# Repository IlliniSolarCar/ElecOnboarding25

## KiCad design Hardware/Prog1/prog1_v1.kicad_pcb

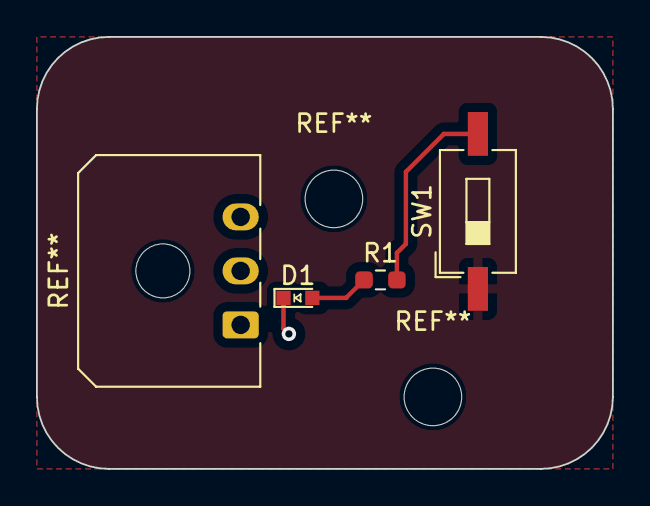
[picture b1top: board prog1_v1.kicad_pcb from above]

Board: 2 copper layers, 32.0 x 24.0 mm, 3 parts (0 on the bottom side), 2 nets.

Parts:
D1: LED_RED; LED_0603_Symbol_on_F.SilkS
R1: 105; R_0603_1608Metric_Pad0.98x0.95mm_HandSolder
SW1: SW_Push; SW_DIP_SPSTx01_Slide_6.7x4.1mm_W8.61mm_P2.54mm_LowProfile

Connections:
unnamed: D1.2 (A), R1.2
unnamed: R1.1, SW1.2

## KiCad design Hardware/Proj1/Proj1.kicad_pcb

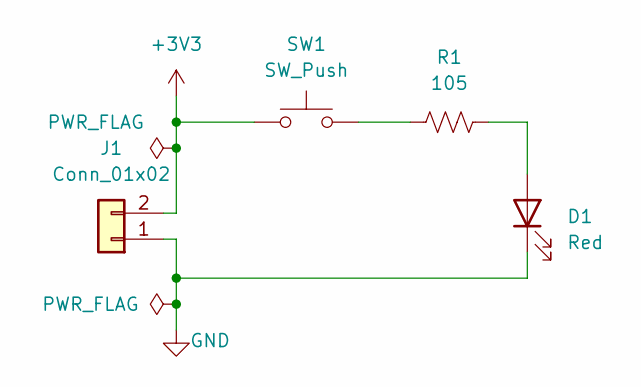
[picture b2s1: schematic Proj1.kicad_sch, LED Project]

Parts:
D1: Red; LED_0603_Symbol_on_F.SilkS
J1: Conn_01x02; Molex_KK-254_AE-6410-02A_1x02_P2.54mm_Vertical; MPN 22-27-2021
R1: 105; R_0603_1608Metric_Pad0.98x0.95mm_HandSolder
SW1: SW_Push; SW_PUSH_6mm; MPN B3F-1000

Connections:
+3V3: J1.2, SW1.1
GND: D1.1 (K), J1.1
unnamed: D1.2 (A), R1.2
unnamed: R1.1, SW1.2

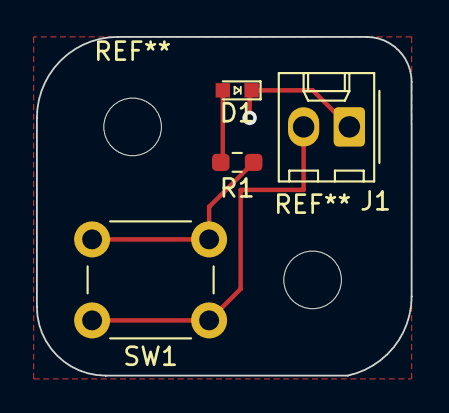
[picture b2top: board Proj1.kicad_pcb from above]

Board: 2 copper layers, 20.8 x 18.8 mm, 4 parts (0 on the bottom side), 4 nets.

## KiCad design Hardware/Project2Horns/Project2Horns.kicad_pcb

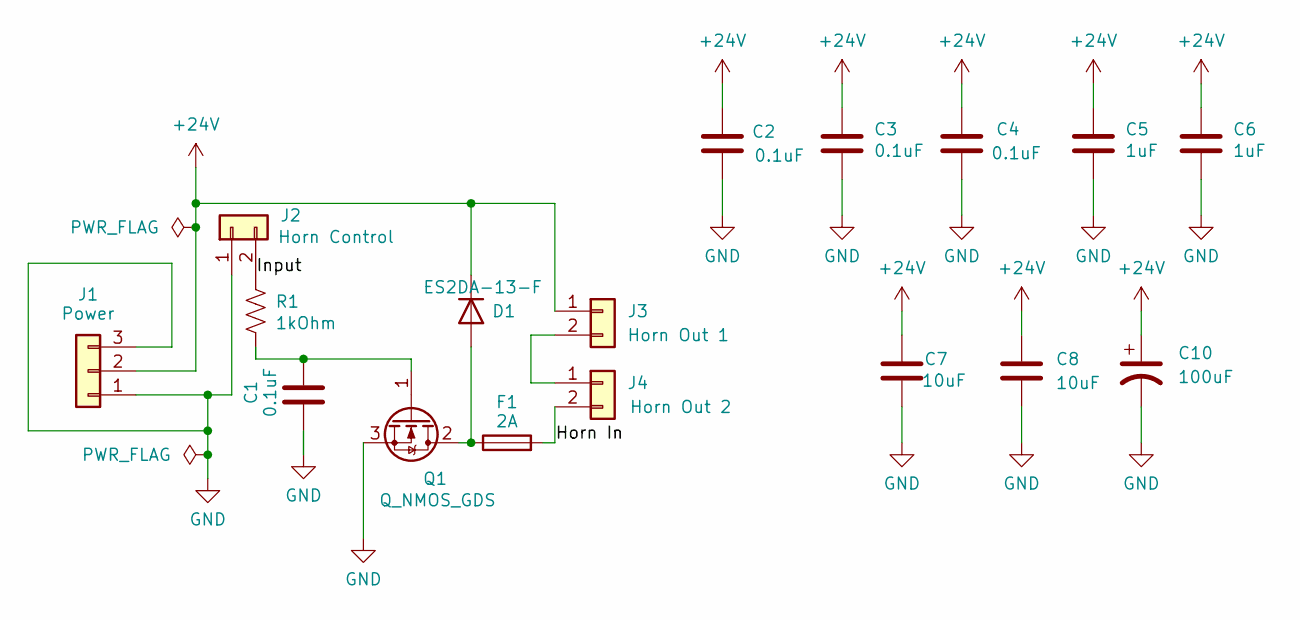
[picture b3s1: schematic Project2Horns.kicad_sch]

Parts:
C1, C2, C3, C4: 0.1uF; C_0603_1608Metric_Pad1.08x0.95mm_HandSolder
C5, C6: 1uF; C_0603_1608Metric_Pad1.08x0.95mm_HandSolder
C7, C8: 10uF; C_0603_1608Metric_Pad1.08x0.95mm_HandSolder
C10: 100uF; CP_Radial_D6.3mm_P2.50mm
D1: ES2DA-13-F; D_SMA_Handsoldering
F1: 2A; Fuse_0603_1608Metric_Pad1.05x0.95mm_HandSolder
J1: Power; Molex_Micro-Fit_3.0_43650-0315_1x03_P3.00mm_Vertical
J2: Horn Control; Molex_Micro-Fit_3.0_43650-0215_1x02_P3.00mm_Vertical
J3: Horn Out 1; Molex_Micro-Fit_3.0_43650-0215_1x02_P3.00mm_Vertical
J4: Horn Out 2; Molex_Micro-Fit_3.0_43650-0215_1x02_P3.00mm_Vertical
Q1: Q_NMOS_GDS; TO-252-2
R1: 1kOhm; R_0603_1608Metric_Pad0.98x0.95mm_HandSolder

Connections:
+24V: C2.1, C3.1, C4.1, C5.1, C6.1, C7.1, C8.1, C10.1, D1.1 (K), J1.2, J3.1
/Horn In: F1.2, J4.2
/Input: J2.2, R1.1
GND: C1.2, C2.2, C3.2, C4.2, C5.2, C6.2, C7.2, C8.2, C10.2, J1.1, J1.3, J2.1, Q1.3 (S)
unnamed: D1.2 (A), F1.1, Q1.2 (D)
unnamed: J3.2, J4.1
unnamed: C1.1, Q1.1 (G), R1.2

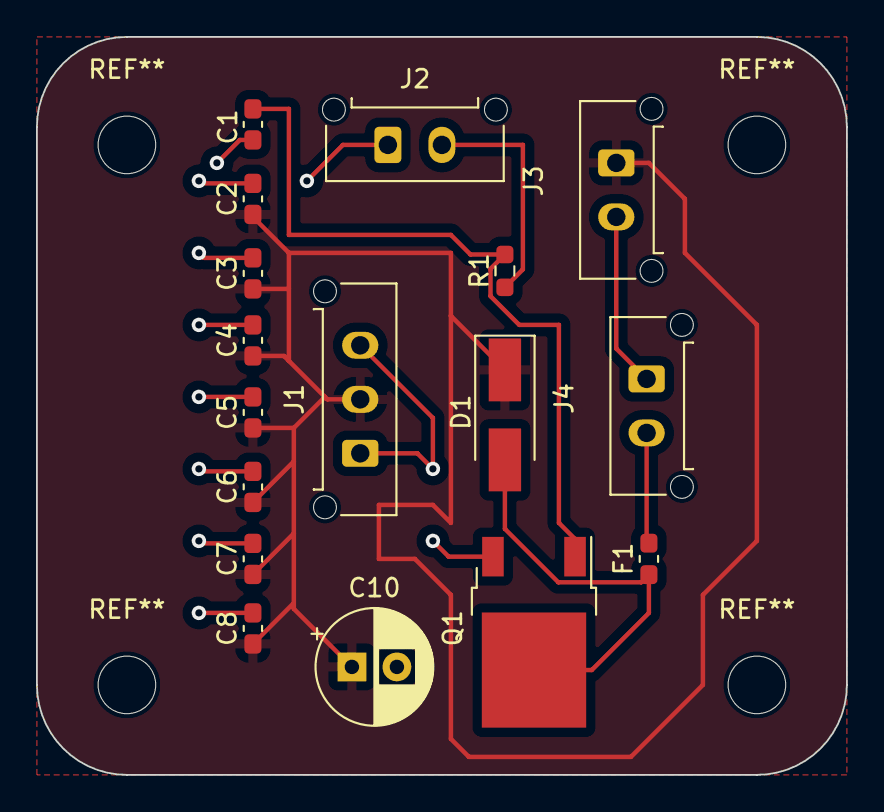
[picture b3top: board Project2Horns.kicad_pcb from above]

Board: 2 copper layers, 45.0 x 41.0 mm, 17 parts (0 on the bottom side), 7 nets.
